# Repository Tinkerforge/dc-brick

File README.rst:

DC Brick
========

This repository contains the firmware source code and the hardware design
files. The documentation generator configs can be found at
https://github.com/Tinkerforge/generators

Repository Content
------------------

software/:
 * examples/: Examples for all supported languages
 * build/: Compiled files
 * src/: Source code of firmware
 * Makefile: Makefile to build project

hardware/:
 * Contains KiCad project files and additionally schematics as PDF

datasheets/:
 * Contains datasheets for sensors and complex ICs that are used

Hardware
--------

The hardware is designed with the open source EDA Suite KiCad
(http://www.kicad.org). Before you are able to open the files,
you have to install the Tinkerforge kicad-libraries
(https://github.com/Tinkerforge/kicad-libraries). You can either clone
them directly in hardware/ or clone them in a separate folder and
symlink them into hardware/
(ln -s kicad_path/kicad-libraries project_path/hardware). After that you
can open the .pro file in hardware/ with KiCad and from there view and
modify the schematics and the PCB layout.

Software
--------

If you want to do your own Brick/Bricklet firmware development we highly
recommend that you use our build environment setup script and read the
tutorial (https://www.tinkerforge.com/en/doc/Tutorials/Tutorial_Build_Environment/Tutorial.html).

To compile the C code we recommend you to install the newest GNU Arm Embedded
Toolchain (https://launchpad.net/gcc-arm-embedded/+download).
You also need to install bricklib (https://github.com/Tinkerforge/bricklib).

You can either clone it directly in software/src/ or clone it in a
separate folder and symlink it into software/src/
(ln -s bricklib_path/bricklib project_path/software/src/). Finally make sure to
have CMake installed (http://www.cmake.org/cmake/resources/software.html).

After that you can build the firmware by invoking make in software/.
The firmware (.bin) can then be found in software/build/ and uploaded
with brickv (click button "Flashing" on start screen).

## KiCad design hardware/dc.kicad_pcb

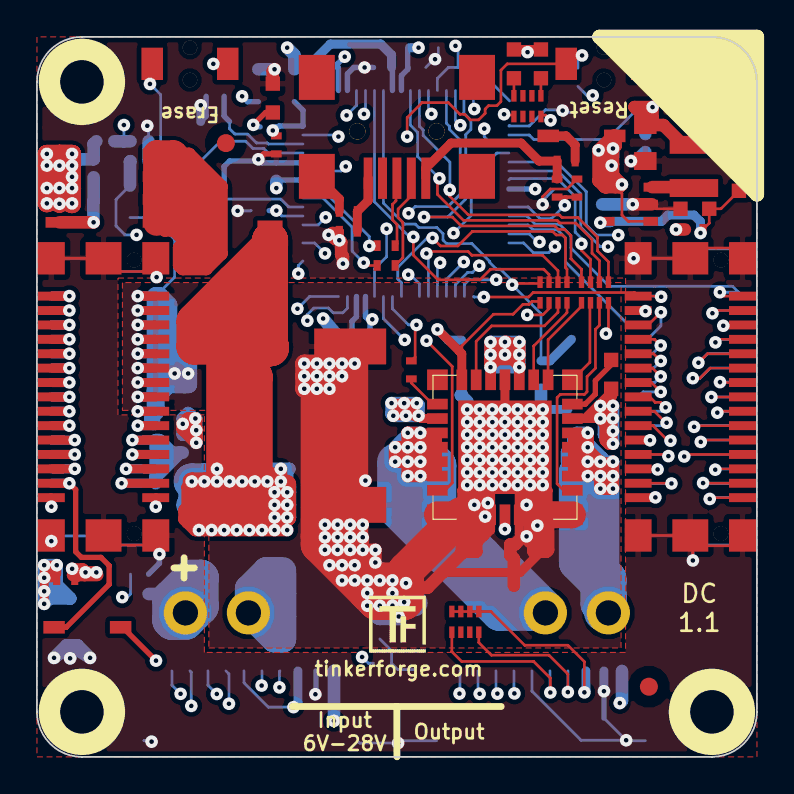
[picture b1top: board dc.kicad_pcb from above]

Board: 4 copper layers, 40.0 x 40.0 mm, 92 parts (0 on the bottom side), 102 nets.

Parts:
C1, C2: 9pF; C0402
C3, C4: 220µF/35V; ELKO_83
C5: 470nF; C0603
C6: 100nF; C0603
C7: 100µF; 3528-21
C8, C10: 10µF; C0805
C9, C12, C13, C14, C16, C17, C19, C20, C22, C24, C25: 100nF; C0402
C11, C23: 4.7µF; C0603
C15: 2.2µF; C0603
C18: DNP; C0402
C21: 10µF/10V; C0805
D1: blue; D0603
D2: red; D0603
D3: Z12V; SOD-123
D4, D5: PMEG4050BEP; SOD-128
D6, D9: Z3.3V; SOD-123
D7, D8: B0520LW-7-F; SOD-123
FB1, FB2, FB3, FB4, FB5: FB; C0402
Fiducial_Mark: VAL**; Fiducial_Mark
Fiducial_Mark#2, Fiducial_Mark#3, Fiducial_Mark#4: VAL**; Fiducial_Mark
J1, J2, J3, J4: DRILL; DRILL_NP
J5: USB-MINI-B-SMD
J6, J8: STACK-UP-HIGH; BTB08-ACS-TOP
J7, J9: STACK-DOWN; BTB08-ACS-BTM
L1: NR3015T4R7M; NR3030
L2: LBR2012T100K; C0805
P1: black; OQ_2P
P2: green; OQ_2P
P3, P4: CON-SENSOR
Q1: FDS8449; SOIC-8-MOSFET
Q2: AO4421; SOIC-8-MOSFET
Q3: 2N7002; SOT23GDS
R1, R2: 27; R0402
R3: 1.8k; R0402
R4: 2.7k; R0402
R5, R8, R10: 10k; R0402
R6, R11, R12, R13, R15: 1k; R0402
R7: 100k; R0402
R9: FB; C0603
R14: 220; R1206
R16: 0; R0603
R17: DNP; R0603
R18: 1R0; R0402
RP1, RP2, RP3, RP4: 1k; 4X0402
Ref**: Val**
SW1: Reset; TACT-SWITCH
SW2: Erase; TACT-SWITCH
U1: AT91SAM3SXB; LQFP64
U2: MC33926; PQFN-32
U3: EUP3406; SOT23-5
VAL: CE_5mm
VAL#2: WEEE_7mm
X1: 16Mhz; CRYSTAL_3225

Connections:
3V3: C8.1, C9.1, C11.1, C12.1, C13.1, C14.1, C18.1, C21.1, C22.1, C25.1, D1.1, D2.1, D7.1, D9.2, J6.20, L1.2, P3.3, P3.6, P4.3, R16.1, RP4.1, RP4.2, RP4.3, RP4.4, SW2.2, U1.1, U1.7, U1.18, U1.45, U1.58
BRICKLET-I2C-SCL: P3.4, P4.4, RP4.8, U1.36
BRICKLET-I2C-SDA: P3.5, P4.5, RP4.5, U1.43
BRICKLET-IO0_0/AD0: P3.7, U1.3
BRICKLET-IO0_1/DA0: P3.8, U1.59
BRICKLET-IO0_2/PWM0: P3.9, U1.20
BRICKLET-IO0_3: P3.10, U1.48
BRICKLET-IO1_0/AD1: P4.7, U1.4
BRICKLET-IO1_1/DA1: P4.8, U1.63
BRICKLET-IO1_2/PWM1: P4.9, U1.19
BRICKLET-IO1_3: P4.10, U1.47
GND: C1.2, C2.2, C7.2, C8.2, C9.2, C10.2, C11.2, C12.2, C13.2, C14.2, C15.2, C16.2, C17.2, C19.2, C20.2, C21.2, C22.2, C23.2, C24.2, C25.2, D9.1, FB1.1, FB4.2, J6.EP, J7.EP, J8.EP, J9.EP, P3.2, P3.EP, P4.2, P4.6, P4.EP, R4.1, R6.2, R9.2, R11.2, R12.1, R17.2, SW1.2, U1.2, U1.17, U1.46, U1.60, U3.2, X1.3
unnamed: C6.2, U2.32
unnamed: C15.1, C16.1, C17.1, C19.1, C20.1, L2.1, U1.8, U1.12, U1.24, U1.54
unnamed: C18.2, R16.2, R17.1, U3.5
unnamed: C23.1, R18.1
unnamed: C24.1, L2.2, R18.2, U1.64
unnamed: D1.2, RP1.1
unnamed: D2.2, RP1.4
unnamed: D3.2, Q1.G, R7.2
unnamed: D4.1, P1.1, R7.1, R10.1
unnamed: D5.1, Q2.D
unnamed: D7.2, J8.28, J9.28
unnamed: FB1.2, FB2.1, J5.5
unnamed: FB2.2, J5.6
unnamed: FB3.2, J5.1, R3.1
unnamed: FB4.1, J8.21, J8.23, J8.25, J8.27, J9.21, J9.23, J9.25, J9.27
unnamed: FB5.2, J8.22, J8.24, J8.26, J9.22, J9.24, J9.26
unnamed: J5.2, R1.1
unnamed: J5.3, R2.1
unnamed: J6.6, J7.8
unnamed: J6.7, J7.7, R15.1
unnamed: J6.8, J7.10
unnamed: J6.10, J7.12
unnamed: J6.12, J7.14
unnamed: J6.13, J7.13
unnamed: J6.14, J7.16
unnamed: J6.15, J7.15
unnamed: J6.16, J7.18
unnamed: J6.17, J7.17
unnamed: J6.18, J7.20
unnamed: J6.22, J7.22
unnamed: J6.24, J7.24
unnamed: J6.25, J7.25
unnamed: J6.27, J7.27
unnamed: J6.29, J7.29
unnamed: J6.30, J7.30
unnamed: J8.29, J9.29
unnamed: J8.30, J9.30
unnamed: L1.1, U3.3
unnamed: P1.2, Q1.D
unnamed: P2.1, U2.12, U2.13, U2.14, U2.15
unnamed: P2.2, U2.27, U2.28, U2.29, U2.30
unnamed: Q2.G, Q3.D, R8.1
unnamed: R1.2, U1.56
unnamed: R2.2, U1.57
unnamed: R13.2, U2.10
unnamed: R14.1, RP3.5, U2.8
unnamed: RP1.5, U1.29
unnamed: RP1.8, U1.30
unnamed: RP2.5, U2.2
unnamed: RP2.6, U2.1
unnamed: RP2.7, U2.26
unnamed: RP2.8, U2.16
unnamed: RP3.6, U2.21
unnamed: RP3.7, U2.7
unnamed: RP3.8, U2.3
unnamed: SW2.1, U1.55
PWR-D1: RP2.2, U1.9
PWR-D2: RP2.1, U1.10
PWR-EN: R13.1, U1.42
PWR-FB: C5.1, D6.2, RP3.4, U1.6
PWR-IN1: RP2.4, U1.15
PWR-IN2: RP2.3, U1.23
PWR-INV: RP3.1, U1.41
PWR-SLEW: RP3.2, U1.38
PWR-STATUS: RP3.3, U1.5
PWR-VEXT: R10.2, R11.1, U1.13
PWR-VSTACK: R5.2, R6.1, U1.16
PWR-VSTACK-SW: Q3.G, R12.2, U1.37
STACK-DETECT/JTAG-TMS: J6.9, J7.9, U1.51
STACK-I2C-SCL/JTAG-TDO: J6.4, J7.4, U1.49
STACK-I2C-SDA/JTAG-TDI: J6.2, J7.2, U1.33
STACK-PGND: C3.2, C4.2, C5.2, D3.1, D6.1, J8.1, J8.3, J8.5, J8.7, J8.9, J8.11, J8.13, J8.15, J8.17, J8.19, J9.1, J9.3, J9.5, J9.7, J9.9, J9.11, J9.13, J9.15, J9.17, J9.19, Q1.S, Q3.S, R9.1, R14.2, U2.5, U2.17, U2.18, U2.19, U2.20, U2.22, U2.23, U2.24, U2.25, U2.EP
STACK-PVCC: J8.2, J8.4, J8.6, J8.8, J8.10, J8.12, J8.14, J8.16, J8.18, J8.20, J9.2, J9.4, J9.6, J9.8, J9.10, J9.12, J9.14, J9.16, J9.18, J9.20, Q2.S, R5.1, R8.2
STACK-RESET: R15.2, SW1.1, U1.39
STACK-SER-RXD: J6.26, J7.26, U1.11
STACK-SER-TXD: J6.28, J7.28, U1.14
STACK-SPI-MISO: J6.1, J7.1, U1.27
STACK-SPI-MOSI: J6.3, J7.3, U1.22
STACK-SPI-SCLK: J6.5, J7.5, U1.21
STACK-SPI-SELECT: J7.6, U1.28
STACK-SYNC/JTAG-TCK: J6.11, J7.11, U1.53
STACK-nINT0: J6.19, J7.19, U1.44
STACK-nINT1: J6.21, J7.21, U1.35
STACK-nINT2: J6.23, J7.23, U1.34
USB-DETECT: R3.2, R4.2, U1.26
VPP: C3.1, C4.1, C6.1, D4.2, D5.2, U2.4, U2.6, U2.11, U2.31
VSTACK: C7.1, C10.1, D8.2, FB5.1, P3.1, P4.1, U3.1, U3.4
VUSB: D8.1, FB3.1
XIN: C2.1, U1.62, X1.2
XOUT: C1.1, U1.61, X1.1

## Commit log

2011-08-25 initial hardware source commit
2011-08-25 add project description
2011-08-25 change voltage epsilon from 200mV to 1000mV
2011-08-26 do configuration of power management only once
2011-08-26 remove adc tc and fix wrong pin for bricklet port
2011-08-26 fix wrong pullup for powerswitching (1k -> 10k) add missing licence comment in brd file
2011-08-26 change diode PMEG1020EH -> B0520LW-7-F
2011-08-26 schematic adapted, since diode was changed
2011-08-31 fix typo in examples
2011-09-06 add red led error status code
2011-09-08 use voltage epsilon to switch between external and stack voltage
2011-09-13 fix typo in c bindings
2011-09-13 add java bindings and examples
2011-09-14 limit line length of java examples to 100 characters
2011-09-15 fix copy and paste fail in java example comments
2011-09-26 Add C# examples and bindings
2011-10-05 Remove Bindings and IP Connection (these are generated and they change too often) and rename bindings to examples
2011-10-05 add tinkerforge package to python imports
2011-10-06 remove faulty gcc commandline invocation
2011-10-06 add firmware version and name
2012-02-13 checkin of Version V1.0 no major things changed - fiducials on board
2012-02-13 fix broken version numbers in schematics
2012-02-14 add compatability for different tick types
2012-02-15 Add changelog
2012-03-05 Fix bug with timeouts on windows (through bricklib)
2012-03-11 Fix bug with ADC calibration readout (through bricklib)
2012-04-25 Unify capitalization of "IP connection" in examples
2012-05-09 Add PHP examples
2012-05-11 php: Use proper capitalization for setPWMFrequency method
2012-05-14 java: Remove unnecessary new String(...) calls
2012-05-25 Add Ruby examples
2012-06-05 Fix register_callback syntax error in Ruby examples on Windows
2012-06-12 Prefer IPConnection destroy over join_thread
2012-06-29 Add get_temperature and reset function (through bricklib)
2012-07-01 Add generate_makefile.bat for windows
2012-07-02 update to newest cmsis core_m3 files (through bricklib)
2012-07-02 Add usb hotplug support (through bricklib)
2012-07-02 Fix USB product description
2012-07-11 Add averaging for current measurement
2012-07-24 Add Delphi examples
2012-07-25 Fix typos in C/C++ examples
2012-07-25 delphi: Set apptype
2012-08-08 delphi: Add comment about UID
2012-09-07 Ignore temporary build files
2012-09-20 Set Interrupt pins to default (otherwise they can interfere with WIFI)
2012-10-08 Fix typo in changelog
2012-10-10 Remove unused define
2012-10-17 Add hardware name for compatibility with new bricklib
2012-10-24 Make cmake find the correct objcopy binary
    On some systems cmake uses the wrong objcopy binary, tell it to use
    the correct one.
2012-10-26 Change Bricklet Context size from 250 to 256 (through bricklib)
2012-11-13 Support for protocol 2.0
2012-11-22 Add compatability for newest bricklib verison
2012-11-22 Reenumerate after USB reconnect
2012-11-29 Make Python examples compatible to Protocol V2.0
2012-11-29 Make Ruby examples Protocol 2.0 compatible
2012-11-29 Make C examples Protocol 2.0 compatible
2012-11-29 Make Java examples Protocol 2.0 compatible
2012-11-29 Make PHP examples Protocol 2.0 compatible
2012-11-29 Make Delphi/Pascal examples Protocol 2.0 compatible
2012-11-30 Add invalid parameter check to set_drive_mode
2012-11-30 delphi: Remove unnecessary parentheses and call destructor again
2012-12-05 Add protocol 2.0 compatability to C# bindings
2012-12-06 Fix C example
2012-12-07 Fix Java example
2012-12-11 Avoid g++ warnings about missing casts in C examples
2012-12-13 Use user data parameter in PHP examples
2013-01-09 Use specific device object for callbacks
2013-01-14 Adapt Java examples to latest IP Connection API
2013-01-16 Update Java example and use a final local instead of a global static variable
2013-01-17 Make Java examples compatible to new listener approach
2013-02-07 Use IPconnection disconnect explicitly in examples
2013-02-14 Fix typo in C# example
2013-02-18 Add Visual Basic .NET examples
2013-04-11 Add watchdog and currently unused support for encoder
2013-06-27 Use tick_task to detect usb connect/disconnect instead of interrupt (through bricklib)
2013-08-09 Add shell examples
2013-08-21 windows: Don't trigger a build in generate_makefile.bat
    Also use normal make instead of a special named one.
2014-01-10 Add Perl examples
2014-01-14 perl: Fix warning about unsharing the $dc variable
2014-01-15 php: Use const for constant values
2014-02-07 Add Mathematica examples
2014-02-10 perl: fixed namespace
2014-02-11 javascript: adding examples
2014-02-11 javascript: short examples
2014-02-18 javascript: examples fixed
2014-02-20 javascript: add html examples
2014-02-24 javascript: port 4280, startExample()
2014-02-28 Fix typo
2014-02-28 javascript: Break long lines and cleanup whitespace
2014-03-05 Add LabVIEW examples
2014-03-06 labview: Add examples in LV2010 format
2014-04-02 java: Unify constants style
2014-04-02 perl: Unify print style
2014-04-16 matlab: add examples
2014-04-17 matlab: Adapt examples to new callback style
2014-04-17 matlab: Add parentheses to make pygments happy
2014-06-12 change voltage divider for usb detect add errata file
2014-07-07 Remove USB hotplug support (through bricklib)
2014-07-15 java: Replace System.console() usage with an Eclipse compatible pattern
2014-11-25 Use new SPI protocol
2014-11-25 Add changelog for v2.3.0
2014-12-02 Use ReadLine instead of ReadKey for C# example
2015-01-19 python: Stop motor before ending program
    This should be done in all other examples as well.
2015-01-19 examples: Stop motor before ending program
2015-02-13 vbnet: Use ReadLine instead of ReadKey
    Because ReadKey doesn't work with a pipe as stdin on the RED Brick.
2015-03-02 windows: Stop cmake from searching for mingw32-make.exe
    Using MinGW Makefiles as generator makes cmake search for mingw32-make.exe
    which might not be installed because GnuWin32's make.exe is used instead.
2015-04-09 c: Whitespace
2015-06-24 javascript: Clean up output creation
2015-06-29 octave: Handle short difference between Octave 3.6 and 3.8
    In Octave 3.6 a short is not automatically handled as a number.
2015-07-23 Make JavaScript browser example textarea readonly
2015-07-27 Cleanup C/C++, C#, Java, Python and Ruby examples
2015-07-28 Simplify exception handling in Java example
2015-07-28 Whitespace
2015-07-29 Reformat changelog
2015-08-07 Use full device class name in Python examples
2015-08-12 Fix minor warnings in C/C++ examples
2015-08-14 Cleanup Delphi examples
2015-08-18 Cleanup VB.NET examples
2015-08-19 Cleanup Perl examples
2015-09-09 Duplicate cmake call to fix bug during cmake creation
2015-09-30 Generator based example cleanup
2015-11-12 matlab: Fix callback handling for R2014a
    http://undocumentedmatlab.com/blog/matlab-callbacks-for-java-events-in-r2014a
2015-11-25 Include date and commit into changelog
2016-04-04 Always set PWM when changing dc_velocity
    Otherwise the PWM setting and the dc_velocity can get out-of-sync.
    For example, enable motor, set dc_velocity_goal > 0 (tick sets
    dc_velocity > 0), disable motor (dc_velocity = 0, but PWM stays > 0),
    set dc_velocity_goal = 0, enable motor. Now the tick sees that
    dc_velocity_goal == dc_velocity == 0 and doesn't change PWM. PWM
    stays > 0 even if it should be 0.
2016-04-04 Add commit to changelog after the fact
2016-05-18 c: Add missing device destroy call
2016-07-01 Make the change UID comment more explicit
2016-08-29 Make sure to use all chunks when writing firmware
    Change through Bricklib
2016-08-29 Fix changelog date
2016-08-29 Better chnagelog wording
2016-12-05 Add ringbuffer and system timer utility as well as co_mcu support files to Makefile (all added through bricklib)
2016-12-28 add hint for connector placement
2017-01-06 Add COM_MESSAGE_USER_LAST_FID define (needed for newest bricklib)
2017-04-13 csharp: Adapt example
2017-04-20 shell: Adapt example
2017-05-11 Add support for co-mcu Bricklets
2017-05-11 Add ref for last changelog entry
2017-06-02 octave: Use javaObject instead of deprecated java_new
2017-06-23 *.brd to *.kicad_pcb
2017-06-23 Add 3d information (tbc), change direction of diodes
2017-06-28 Update changelog and version
2017-06-28 Add tag ref to changelog
2017-06-30 Add 3d information (tbc); fix direction of some diodes
2017-07-07 Add 3d information (final)
2017-07-07 DC Brick: Add 3d model (*.step & *.FCStd)
2017-08-01 Add 3d component: NR3030
2017-11-28 fix partial routing due to footprint size increases
2017-11-28 dc brick version 1.1
    * fix motor connector position
2017-11-28 fix ce and weee logo
2017-11-30 vbnet: Update callback name
2017-11-30 mathematica: Update callback name
2017-12-05 Remove initial USB enumeration (now done in bricklib)
2017-12-05 Increase version, update changelog
2017-12-07 mathematica: Also generate .nb files
2017-12-12 Remove unused include
2017-12-13 Add date and ref to changelog
2018-01-11 Increase version number (message duplication bug fix through bricklib)
2018-01-11 Add ref to changelog
2018-02-19 javascript: Close div tag correctly
2018-02-20 Cleanup KiCad libraries config
    Ensure LibDir=kicad-libraries and LibName1=tinkerforge.
    Remove special library.
2018-04-27 Update version and changelog
2018-04-27 Fix date
2018-04-27 Add git ref to changelog
2018-05-24 perl: Use strict in examples
2018-05-28 mathematica: Fix namespace
2018-07-11 Add Makefile with docker support
2018-07-11 Update directory structure and build instructions
2018-07-11 Remove obsolete generate_makefile scripts
2018-07-20 Add new 3d model
2018-07-31 Increase version and update changelog
2018-07-31 Update changelog ref
2018-11-06 Add rust examples
2018-11-07 rust: Accept host names for ip connection, fix naming inconsistencies
2018-11-07 rust: Rename callback receivers.
2018-12-14 Add go examples.
2018-12-18 go: Change import path.
2018-12-18 go: Change import path again.
2018-12-20 rust: Reformat examples.
2019-01-24 mqtt: Add examples.
2019-01-24 mqtt: Fix example header.
2019-01-24 mqtt: Remove executable bit in example permissions.
2019-01-24 go: Minor example fixes.
2019-01-24 mqtt: Minor example fixes.
2019-02-27 Increase version for new release (changes in bricklib)
2019-02-27 Add rev to changelog
2019-08-22 c: Adapt to bindings changes
2020-01-13 examples: Use python3 input instead of python2 raw_input.
2020-01-13 examples: mqtt: Remove trailing whitespace.
2020-01-14 examples: Use python3 input by default.
2020-03-18 rust: Update to new skeleton
2020-03-19 examples: Properly stop motor before disabling motor power
    Disabling motor power while motor is still running could cause
    hardware damage.
2020-03-19 labview: Use event structure instead of while loop to wait for event
2020-04-07 examples: Add missing imports for sleep calls
2020-04-07 examples: rust: Always block when calling bindings functions.
2020-05-14 Fix response length of get_drive_mode.
2020-05-14 Add commit ref to changelog.
2020-10-06 fixed symbols and schematic
2021-01-14 rust: Break long comment
2021-05-04 octave: Fix wrong function name
2021-10-25 Update KiCad link
    https://www.kicad.org/blog/2021/10/Avoid-links-to-former-kicad-domain/
2022-07-06 Add license files.

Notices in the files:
hardware/dc.kicad_pcb:
Licensed under CERN OHL v.1.1
Copyright (©) 2017, B.Nordmeyer
Copyright Tinkerforge GmbH 2017.
This documentation describes Open Hardware and is licensed under the
CERN OHL v. 1.1.
